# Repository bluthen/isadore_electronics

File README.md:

# isadore_electonics

Design files for the electronics of the Isadore Dryer Management System. Also included is what is called the MID software which queries the electronics and reports it back to the [isadore_server](https://github.com/bluthen/isadore_server/)

# Electronics Manufacture

Electronics manufactures usually want gerbers, centroid file, and a bill of materials. The latest pre-generated versions of these files can usually be found in the out directory (Example: `sensor_unitv3/out/`).

* The centroid and gerbers are in the zip file.
* The bill of materials is in the excel spreadsheet file (xlsx)
* An optional pins.png file may exist to show the manufacturer the location of pin1 for ICs.

Optionally you can generate the gerbers and centroid yourself depending by opening it up in [Eagle](https://www.autodesk.com/products/eagle/overview).

# Electronics Firmware

After you have a sensor unit or sensor hub, you need to program their firmware. To do this you need a AVR ISP programmer. Then there are script to help you program them. `sensor_unitv3/code/make.py`, `sensor_hubv3/code/Makefile`, and `fuse_crystal_clock.sh`.

*Note* you need a 5 pin ISP programmer. Most sold are 10 pin, so an adapter is needed.

To program the units or hubs you need some software installed:

* `avrdude`
* `gcc-avr`
* `avr-libc`

## Sensor Unit
A sensor unit can be programmed in many ways depending on what sensor modules you are going to plug into it.

Here is the help usage for `make.py`

```
Usage: make.py [OPTIONS] ADDRESS
  -h, --help                      Show this screen
  -d, --debug                     Debug build
  -p, --program                   Program unit
  -c, --clean                     Clean
  -f, --fuse                      Set fuse
  --prev303                       Build for prev3.03 unit
  --with-th                       Build with temperature humidty
  --with-pressurev1=m,b           Build in v1 pressure module
  --with-pressurev4a=cal_adjust   Build in v4a pressure module
  --with-pressurev4b=cal_adjust   Build in v4b pressure module
  --with-pressurev5=m,b           Build in v5 pressure module
  --with-anemometer               Build in Anemometer module
  --with-thermo                   Build in thermocouple module
  --with-multit                   Build in Multipoint-temp module
  --with-tach                     Build in tachometer module
```

So for example you might do with a unit, with the programmed placed and the unit powered.
```
python2 make.py -f -c -p --with-pressurev4b=0 102
```

If successful It is now programmed to use the pressurev4 module that gives you pressure/temperature/rh, and responses when address `102` is queried.

## Sensor Hub

To program the hub you would run with the programmer in place and powered:
```
cd sensor_hubv3/code
./fuse_crystal_clock.sh && make program
```

# MID (Master Interface Device)

This is basically the combination of a small computer (raspberry pi) and the hub electronics board. The hub and raspberry pi communicate serially. The hub has voltage regulators to power the raspberry pi.

## HUB<-> pi wiring

Notice for the power, Red is on TP1, and black is outside of usb connector.

Communication headers on pins 4 and 5 from outside corner.

## Install and configure raspbian

After installing raspian you'll want to set to enable access to the serail port with `raspi-config` and [disable the use of console by uart](https://www.raspberrypi.org/documentation/configuration/uart.md).

```
$ raspi-config
Interface Options->Serial->No->Yes
```

You'll also want to make sure the following are installed:

```
apt-get install python python-pip python-dev
pip install flask pytz requests restkit pyserial pymodbus numpy termcolor netifaces netaddr
```

## Troubleshooting
There is a script called `midsim.py` that can aid in troubleshooting. It allows you to query sensors from the command line. It is located at `sensor_hubv3/code/test/midsim.py` 

Below is the usage:

```
Usage: midsim.py [OPTION]...
  -h, --help            show this screen
  -v, --verbose         output verbose debug output
  -c, --continous=t,c   Keep pulling every t seconds, c many times c=0 for infinite
                        default is to pull once.
  -f, --format=format   The output format to use:
                        default:   The default style output
                        csv:       csv style output
  -t, --type=TYPE       TYPE=(temphum|anemometer|tachometer|thermocouple|pressure|pressurewide|
                              multipointreset|multipointc[1-4]|multipointaddrc[1-4]|ping|
                              unitversion|hubversion) *Required
  --get-cal             Get calibration value for type
  --set-cal=CAL_VALUE   Set calibration value for type
  -p, --port=PORT       PORT=#
  -a, --address=ADDRESS ADDRESS=#,#,#,...
  -u                    use udp instead of serial
  -d, --device=PATH     serial device to use for version 3, default /dev/ttyAMA0
  -o                    Use direct command code instead of general (aka version2)
  -j                    Just send commands then exit immediatly
  -s, --server=IP:PORT  Start midsim server listening on IP:PORT
  -r, --remote=IP:PORT  Query remote midsim server on IP:PORT

  address,port required except for --type=ping
  Max number of addresses is 32.
```

## Calibration
The main goal of the pressure modules was to report differencial pressure. The pressure module can be calibrated and there is a script to help with that process. It takes a large amounts of samples and sets an offset to match the reference. This script can be found at `sensor_hubv3/code/test/calibrator.py`

## Configure mid_software

Copy the mid_software to the raspberry pi. Copy `MID.cfg.example` to `MID.cfg` but one directory down from the location of mid_software. Modify MID.cfg for your needs. The most importanted are `baseurl` and `MIDpassword`Below is a reference for what each key means:

* `baseurl` The url to the base location of your running instance of [isadore_server](https://github.com/bluthen/isadore_server/).
* `MIDname` If you have multiple mids, this needs to be set so it knows which config to fetch. If it doesn't exist, all configs are fetched.
* `MIDpassword` The mid password that was set for your instance of isadore_server.
* `configpath` relative url where it should get the systems unit configuration. shouldn't need changing.
* `uploadpath` the relative url it should use to upload sensor data it gets. shouldn't need changing.
* `rcstatuspath` the relative url it uses for controls. shouldn't need changing.
* `hub_serial` the serial port to use to communicate with the hub electronics board. `/dev/ttyAMA0` on old raspberry pi's, `/dev/serial0` on new ones.
* `STORE_RAW_DATA_MODE` shouldn't need changing
* `RAW_DATA_LOC` shouldn't need changing
* `RS485_TIMEOUT` time out per unit. shouldn't need changing
* `RS485_BAUD` The serial baud rate to use. shouldn't need changing
* `enableRC_p` shouldn't need changing
* `mid_reading_interval_seconds` The minimal amount of time to pass before reading sensor data again.
* `log_level` The level to log at, can be `ERROR`, `WARNING`, or `DEBUG`
* `turn_off` If it should be not be activly getting readings and uploading them.

There are also some other configurations for specific temperature controls. For now for those parameters, please see the code to find them.

## Running mid_software

Put the following in the crontab of the user that is going to run mid_software on the MID. Replace the path to where you copied mid_software.

```
*/15 * * * * /home/pi/mid_software/processCheck.sh
*/10 * * * * /home/pi/mid_software/mid_log_check.sh
```

* `processCheck.sh` will start the process if it doesn't find it running.
* `mid_log_check.sh` tries to detect if the process locked up and will restart it, if it thinks it has.

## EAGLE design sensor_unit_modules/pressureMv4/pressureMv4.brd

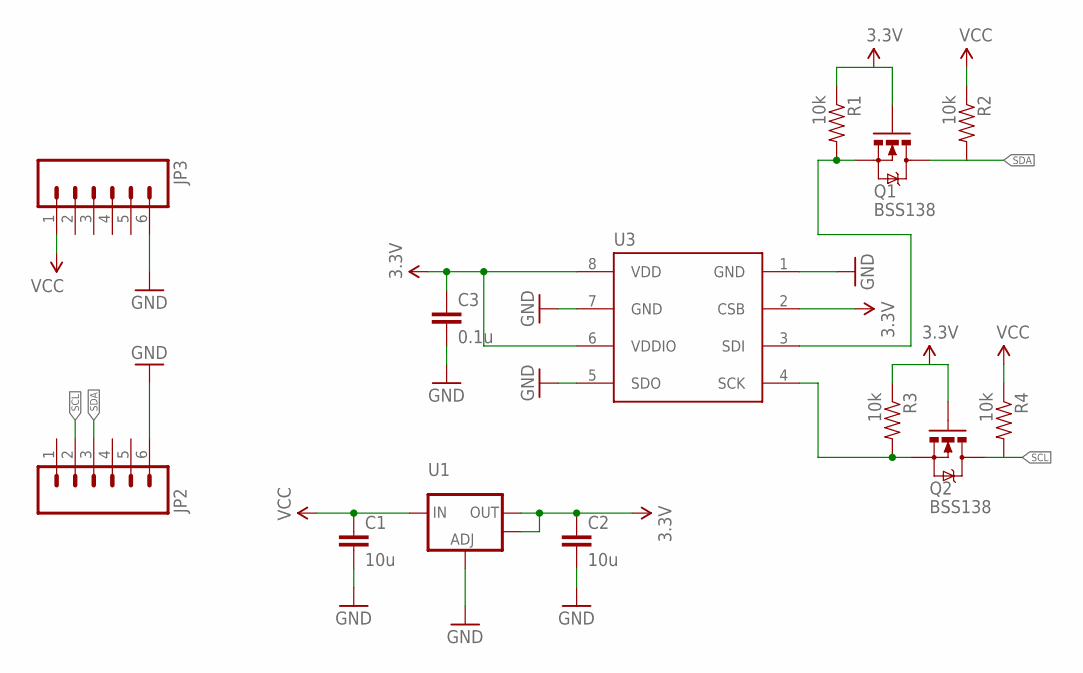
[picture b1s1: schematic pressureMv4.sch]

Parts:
C1, C2: 10u; 0805
C3: 0.1u; 0805
JP2, JP3: M06LOCK_LONGPADS; 1X06_LOCK_LONGPADS
Q1, Q2: BSS138; SOT323
R1, R2, R3, R4: 10k; 0805
U1: V_REG_LM1117SOT223; SOT223
U3: BME280SMD; BME280

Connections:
3.3V: C2.1, C3.1, Q1.1 (G), Q2.1 (G), R1.1, R3.1, U1.2 (OUT), U1.4 (OUT), U3.2 (CSB), U3.6 (VDDIO), U3.8 (VDD)
GND: C1.2, C2.2, C3.2, JP2.6, JP3.6, U1.1 (ADJ), U3.1 (GND), U3.5 (SDO), U3.7 (GND)
unnamed: Q1.2 (S), R1.2, U3.3 (SDI)
unnamed: Q2.2 (S), R3.2, U3.4 (SCK)
SCL: JP2.2, Q2.3 (D), R4.2
SDA: JP2.3, Q1.3 (D), R2.2
VCC: C1.1, JP3.1, R2.1, R4.1, U1.3 (IN)

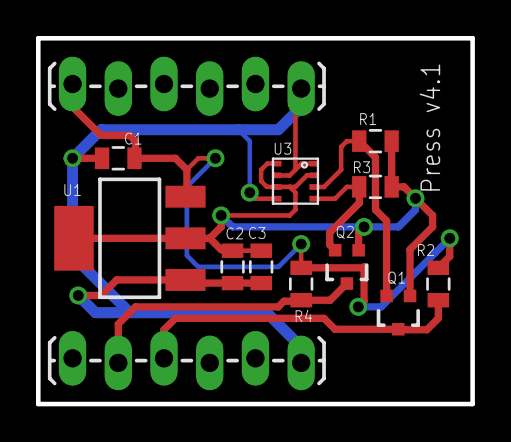
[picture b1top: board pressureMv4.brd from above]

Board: 2 copper layers, 24.1 x 20.3 mm, 13 parts (0 on the bottom side), 7 nets.

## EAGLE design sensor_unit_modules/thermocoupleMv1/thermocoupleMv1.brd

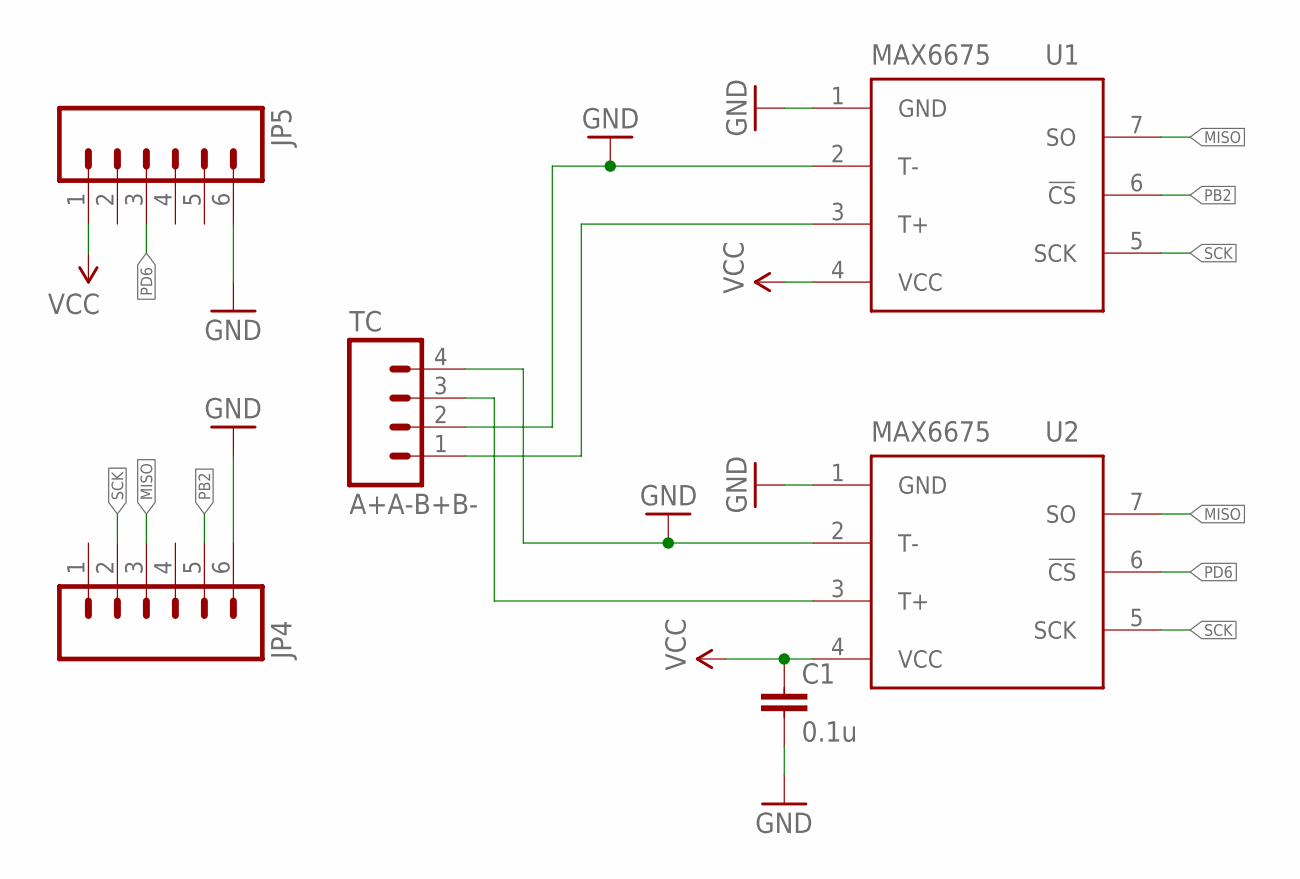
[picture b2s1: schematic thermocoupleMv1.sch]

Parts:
C1: 0.1u; 0805
JP4, JP5: M06LOCK_LONGPADS; 1X06_LOCK_LONGPADS
TC: A+A-B+B-; 1X04_LOCK_LONGPADS
U1, U2: MAX6675; SO08

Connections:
GND: C1.2, JP4.6, JP5.6, TC.2, TC.4, U1.1 (GND), U1.2 (T-), U2.1 (GND), U2.2 (T-)
MISO: JP4.3, U1.7 (SO), U2.7 (SO)
unnamed: TC.1, U1.3 (T+)
unnamed: TC.3, U2.3 (T+)
PB2: JP4.5, U1.6 (!CS)
PD6: JP5.3, U2.6 (!CS)
SCK: JP4.2, U1.5 (SCK), U2.5 (SCK)
VCC: C1.1, JP5.1, U1.4 (VCC), U2.4 (VCC)

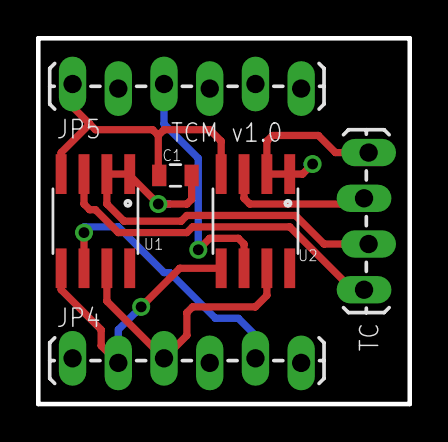
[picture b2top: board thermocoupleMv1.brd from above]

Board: 2 copper layers, 20.6 x 20.3 mm, 6 parts (0 on the bottom side), 8 nets.

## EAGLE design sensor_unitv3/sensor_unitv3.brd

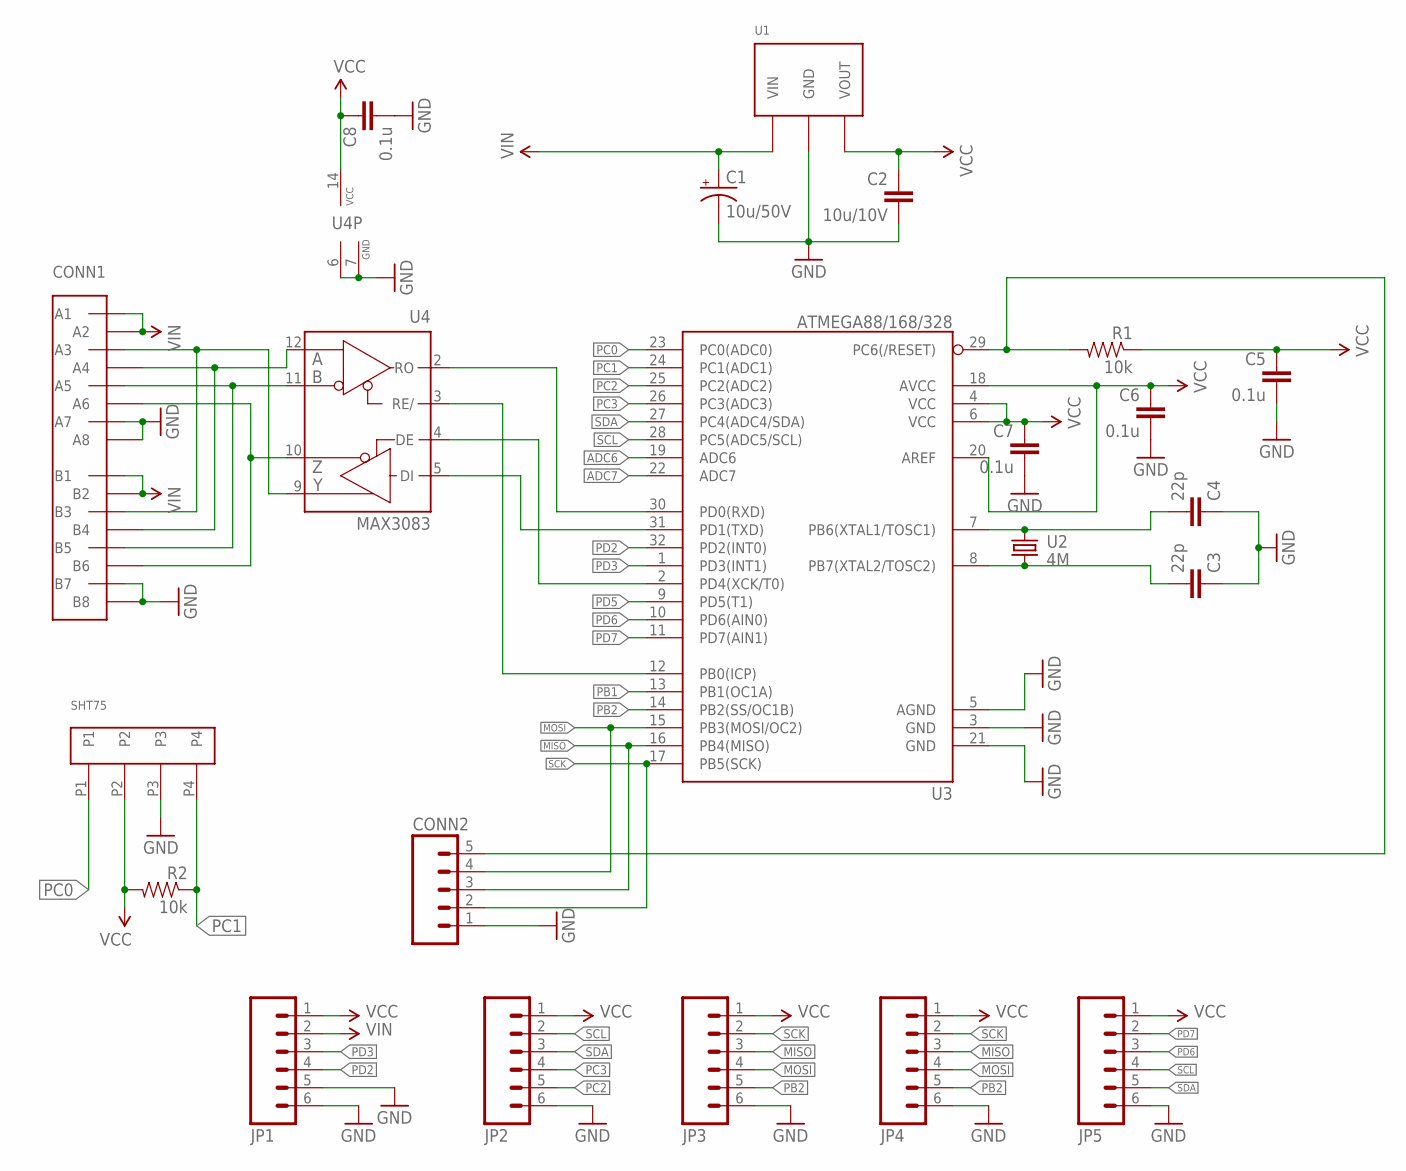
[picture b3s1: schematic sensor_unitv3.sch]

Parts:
C1: 10u/50V; PANASONIC_C
C2: 10u/10V; 0805
C3, C4: 22p; 0805
C5, C6, C7, C8: 0.1u; 0805
CONN1: 4UCON-04950
CONN2: M05LOCK; 1X05_LOCK
JP1, JP2, JP3, JP4, JP5: M06LOCK_LONGPADS; 1X06_LOCK_LONGPADS
R1, R2: 10k; 0805
SHT75: MM852-43-004-20; MM851-43-004-20
U1: OKI-78SR
U2: 4M; HC49UP
U3: ATMEGA88/168/328; TQFP32-08
U4: MAX3083; SO14

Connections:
ADC6: U3.19 (ADC6)
ADC7: U3.22 (ADC7)
C1U49: CONN1.A3, CONN1.B3, U4.9 (Y)
DE: U3.2 (PD4(XCK/T0)), U4.4 (DE)
DI: U3.31 (PD1(TXD)), U4.5 (DI)
GND: C1.-, C2.2, C3.1, C4.1, C5.2, C6.2, C7.2, C8.2, CONN1.A7, CONN1.A8, CONN1.B7, CONN1.B8, CONN2.1, JP1.5, JP1.6, JP2.6, JP3.6, JP4.6, JP5.6, SHT75.P3, U1.GND, U3.3 (GND), U3.5 (AGND), U3.21 (GND), U4.6 (GND), U4.7 (GND)
MISO: CONN2.3, JP3.3, JP4.3, U3.16 (PB4(MISO))
MOSI: CONN2.4, JP3.4, JP4.4, U3.15 (PB3(MOSI/OC2))
unnamed: C3.2, U2.1, U3.8 (PB7(XTAL2/TOSC2))
unnamed: C4.2, U2.2, U3.7 (PB6(XTAL1/TOSC1))
unnamed: CONN1.A5, CONN1.B5, U4.11 (B)
unnamed: CONN1.A4, CONN1.B4, U4.12 (A)
unnamed: CONN1.A6, CONN1.B6, U4.10 (Z)
PB1: U3.13 (PB1(OC1A))
PB2: JP3.5, JP4.5, U3.14 (PB2(SS/OC1B))
PC0: SHT75.P1, U3.23 (PC0(ADC0))
PC1: R2.1, SHT75.P4, U3.24 (PC1(ADC1))
PC2: JP2.5, U3.25 (PC2(ADC2))
PC3: JP2.4, U3.26 (PC3(ADC3))
PD2: JP1.4, U3.32 (PD2(INT0))
PD3: JP1.3, U3.1 (PD3(INT1))
PD5: U3.9 (PD5(T1))
PD6: JP5.3, U3.10 (PD6(AIN0))
PD7: JP5.2, U3.11 (PD7(AIN1))
RE: U3.12 (PB0(ICP)), U4.3 (RE/)
RESET: CONN2.5, R1.2, U3.29 (PC6(/RESET))
RO: U3.30 (PD0(RXD)), U4.2 (RO)
SCK: CONN2.2, JP3.2, JP4.2, U3.17 (PB5(SCK))
SCL: JP2.2, JP5.4, U3.28 (PC5(ADC5/SCL))
SDA: JP2.3, JP5.5, U3.27 (PC4(ADC4/SDA))
VCC: C2.1, C5.1, C6.1, C7.1, C8.1, JP1.1, JP2.1, JP3.1, JP4.1, JP5.1, R1.1, R2.2, SHT75.P2, U1.VOUT, U3.4 (VCC), U3.6 (VCC), U3.18 (AVCC), U3.20 (AREF), U4.14 (VCC)
VIN: C1.+, CONN1.A1, CONN1.A2, CONN1.B1, CONN1.B2, JP1.2, U1.VIN

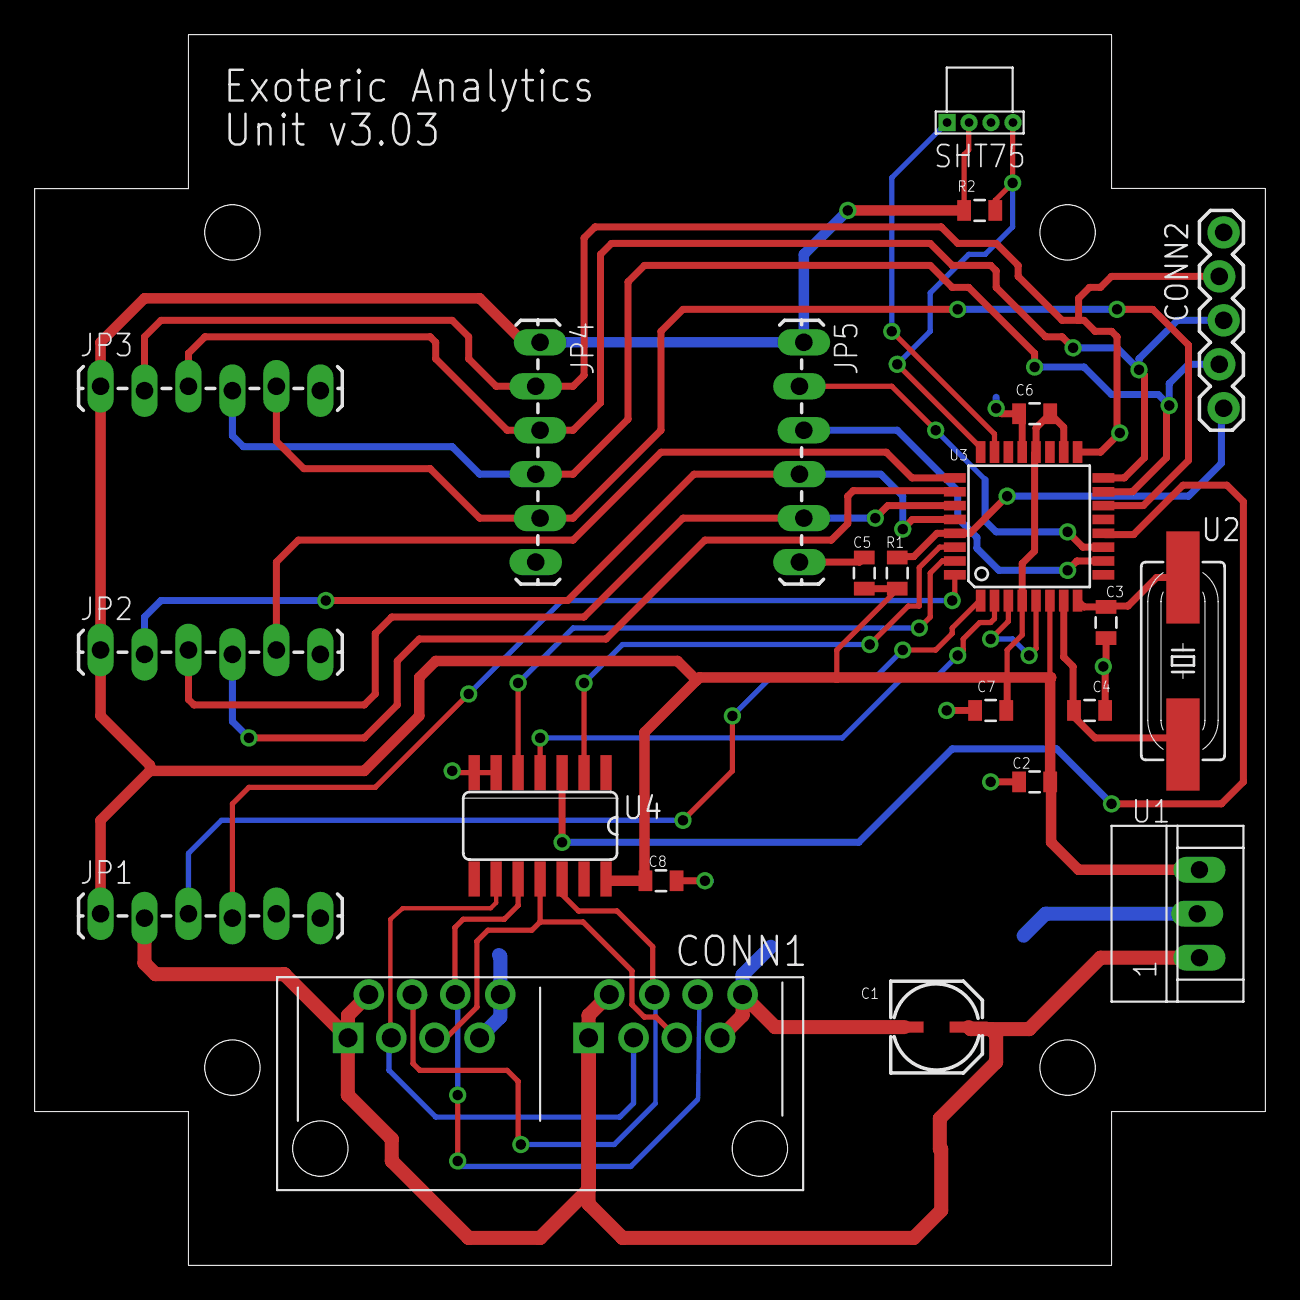
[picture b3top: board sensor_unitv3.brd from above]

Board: 2 copper layers, 71.1 x 71.1 mm, 22 parts (0 on the bottom side), 28 nets.

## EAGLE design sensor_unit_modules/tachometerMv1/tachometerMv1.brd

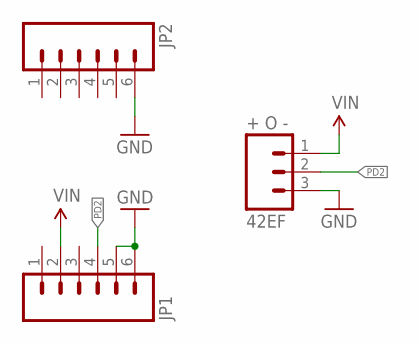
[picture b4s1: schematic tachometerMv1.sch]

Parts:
42EF: + O -; 1X03_LOCK_LONGPADS
JP1, JP2: M06LOCK_LONGPADS; 1X06_LOCK_LONGPADS

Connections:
GND: 42EF.3, JP1.5, JP1.6, JP2.6
PD2: 42EF.2, JP1.4
VIN: 42EF.1, JP1.2

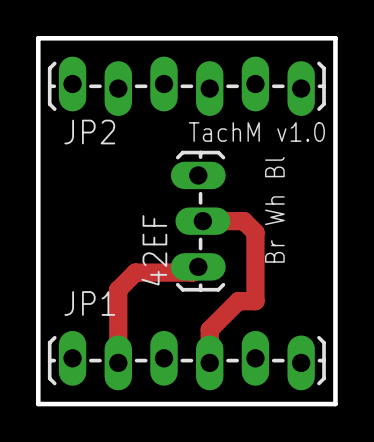
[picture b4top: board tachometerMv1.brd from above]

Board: 2 copper layers, 16.5 x 20.3 mm, 3 parts (0 on the bottom side), 3 nets.

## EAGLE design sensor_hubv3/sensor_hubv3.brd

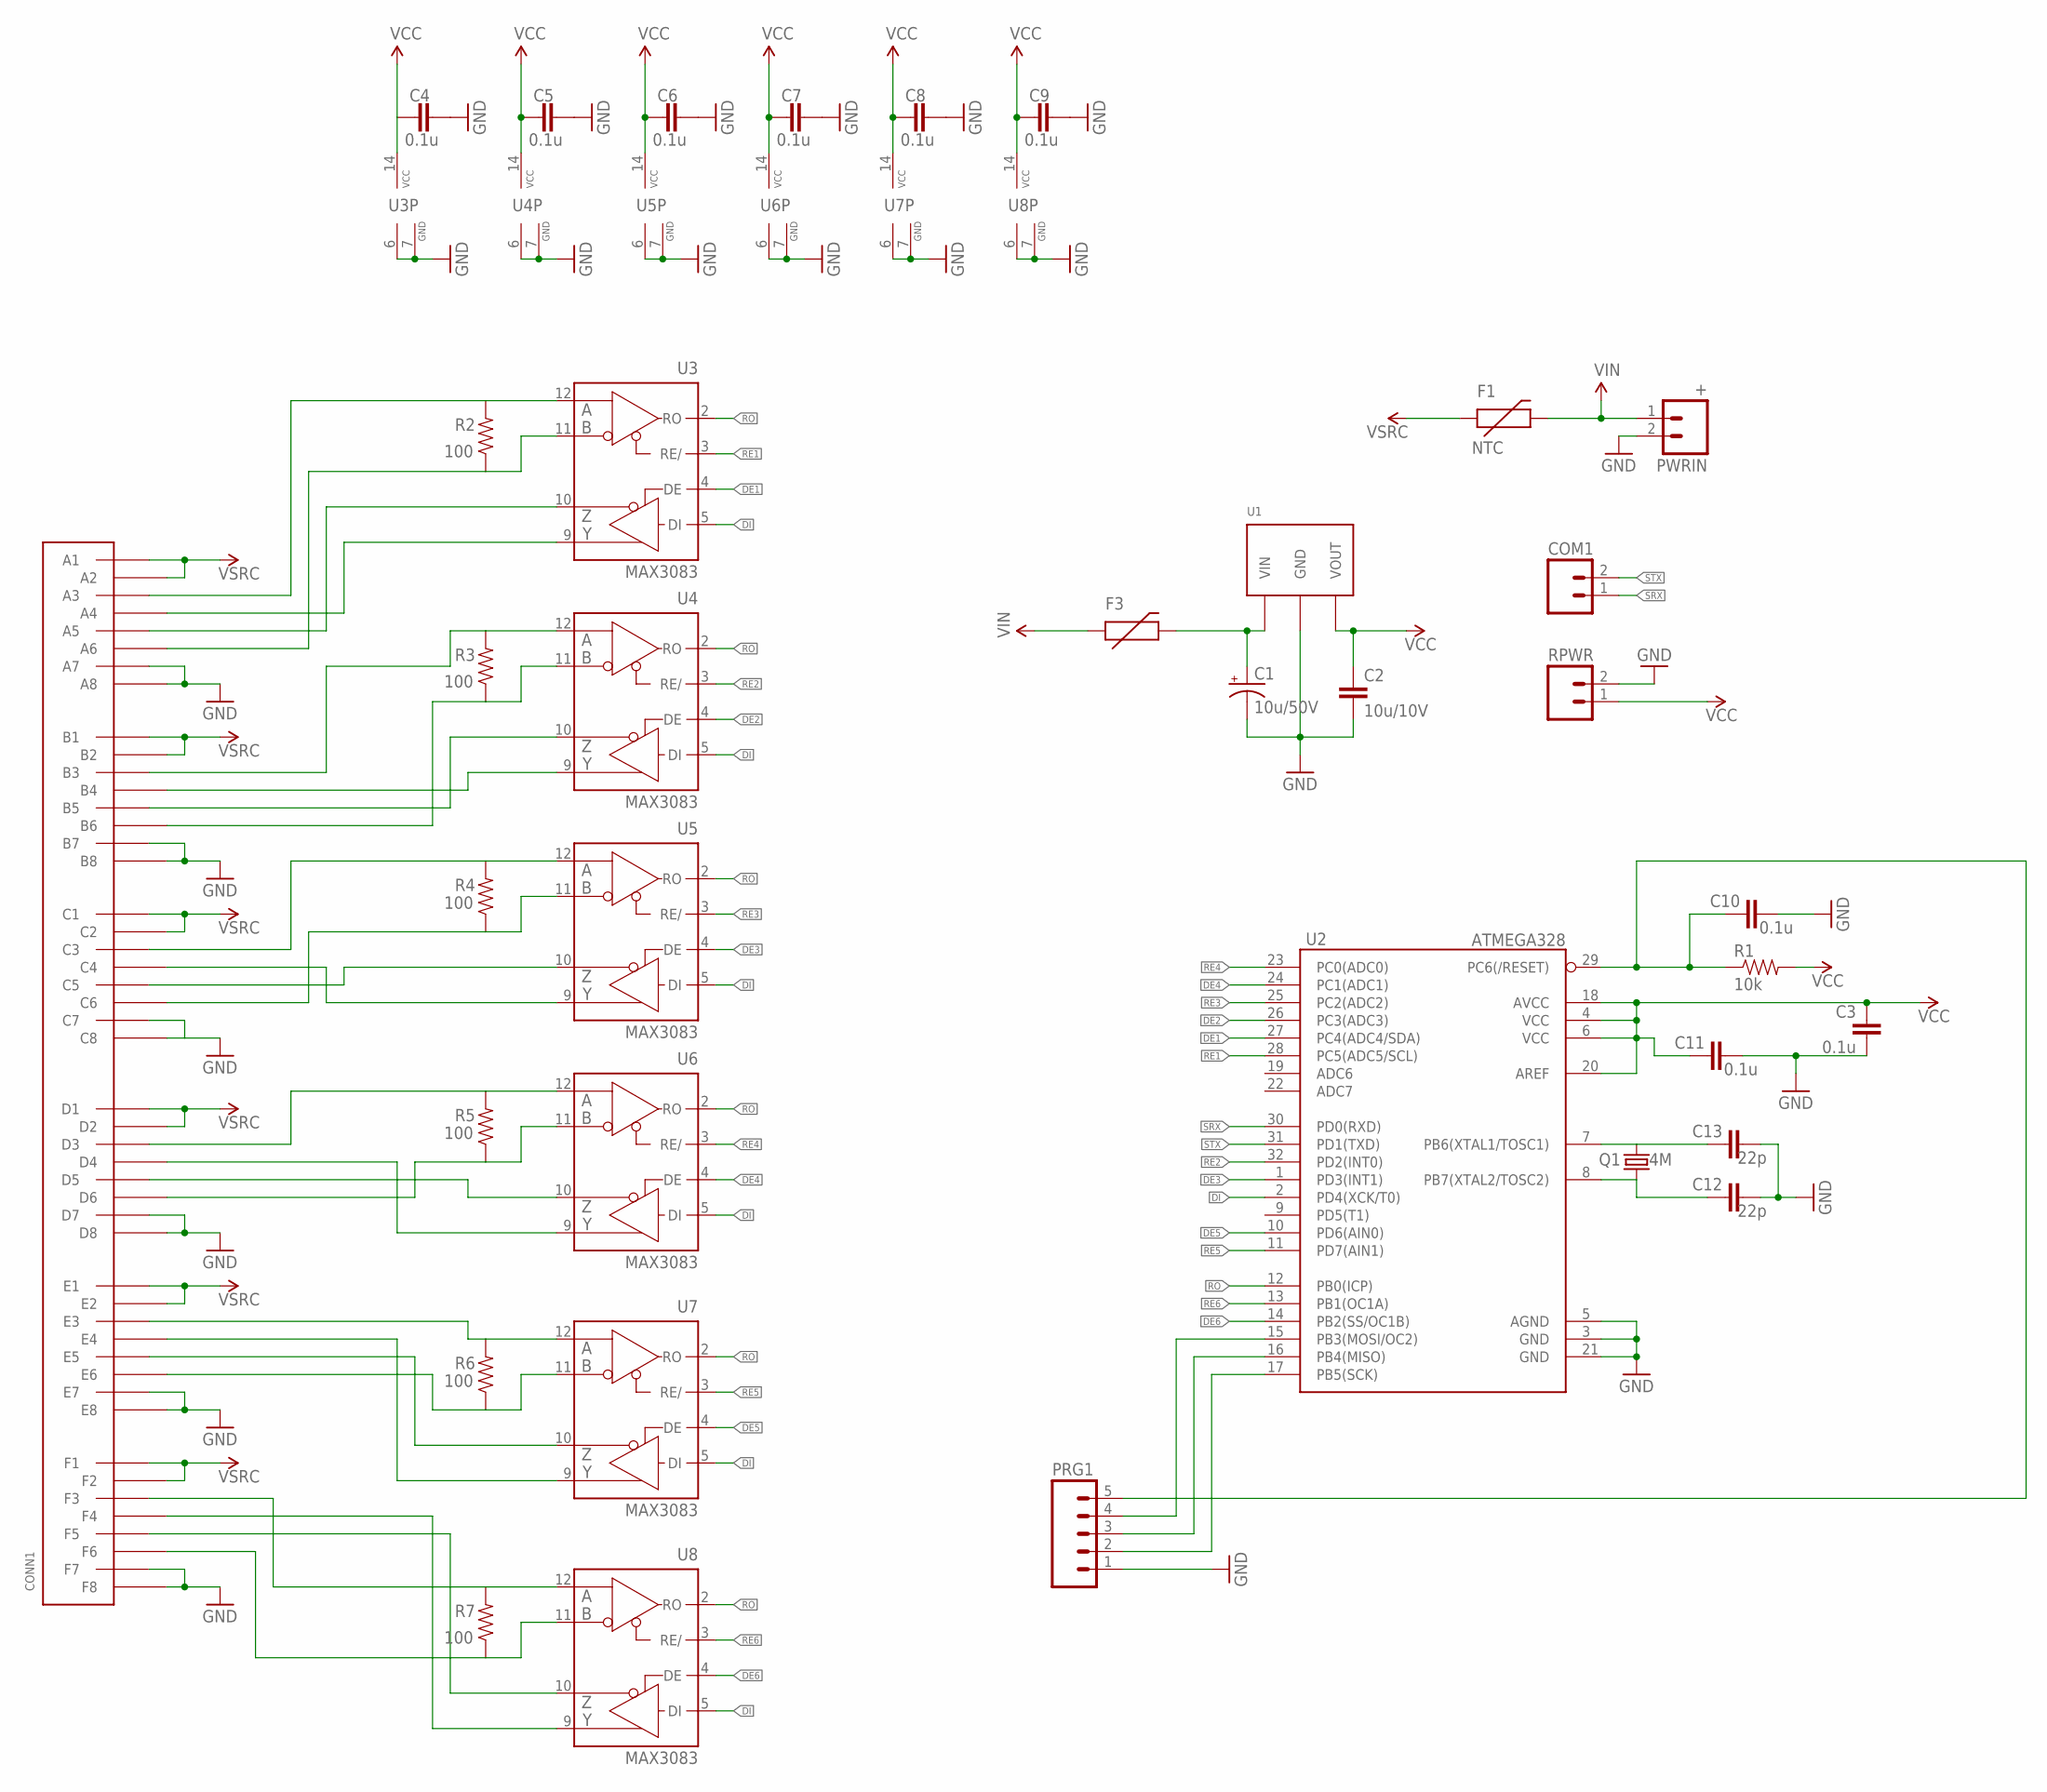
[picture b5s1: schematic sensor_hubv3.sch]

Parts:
C1: 10u/50V; PANASONIC_C
C2: 10u/10V; 0805
C3, C4, C5, C6, C7, C8, C9, C10, C11: 0.1u; 0805
C12, C13: 22p; 0805
COM1: M02LOCK_LONGPADS; 1X02_LOCK_LONGPADS
CONN1: 8P8C-6PORT; 4UCON-04953
F1: NTC; R-7,5
F3: PTC0603; 0603
PRG1: M05LOCK; 1X05_LOCK
PWRIN: +; SCREWTERMINAL-5MM-2
Q1: 4M; HC49UP
R1: 10k; 0805
R2, R3, R4, R5, R6, R7: 100; 0805
RPWR: M02LOCK_LONGPADS; 1X02_LOCK_LONGPADS
U1: OKI-78SR
U2: ATMEGA328; TQFP32-08
U3, U4, U5, U6, U7, U8: MAX3083; SO14

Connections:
DE1: U2.27 (PC4(ADC4/SDA)), U3.4 (DE)
DE2: U2.26 (PC3(ADC3)), U4.4 (DE)
DE3: U2.1 (PD3(INT1)), U5.4 (DE)
DE4: U2.24 (PC1(ADC1)), U6.4 (DE)
DE5: U2.10 (PD6(AIN0)), U7.4 (DE)
DE6: U2.14 (PB2(SS/OC1B)), U8.4 (DE)
DI: U2.2 (PD4(XCK/T0)), U3.5 (DI), U4.5 (DI), U5.5 (DI), U6.5 (DI), U7.5 (DI), U8.5 (DI)
GND: C1.-, C2.2, C3.1, C4.2, C5.2, C6.2, C7.2, C8.2, C9.2, C10.2, C11.2, C12.2, C13.2, CONN1.A7, CONN1.A8, CONN1.B7, CONN1.B8, CONN1.C7, CONN1.C8, CONN1.D7, CONN1.D8, CONN1.E7, CONN1.E8, CONN1.F7, CONN1.F8, PRG1.1, PWRIN.2, RPWR.2, U1.GND, U2.3 (GND), U2.5 (AGND), U2.21 (GND), U3.6 (GND), U3.7 (GND), U4.6 (GND), U4.7 (GND), U5.6 (GND), U5.7 (GND), U6.6 (GND), U6.7 (GND), U7.6 (GND), U7.7 (GND), U8.6 (GND), U8.7 (GND)
unnamed: CONN1.C4, U5.9 (Y)
unnamed: C13.1, Q1.2, U2.7 (PB6(XTAL1/TOSC1))
unnamed: C1.+, F3.2, U1.VIN
unnamed: C12.1, Q1.1, U2.8 (PB7(XTAL2/TOSC2))
unnamed: C10.1, PRG1.5, R1.1, U2.29 (PC6(/RESET))
unnamed: PRG1.4, U2.15 (PB3(MOSI/OC2))
unnamed: PRG1.3, U2.16 (PB4(MISO))
unnamed: PRG1.2, U2.17 (PB5(SCK))
unnamed: CONN1.A3, R2.2, U3.12 (A)
unnamed: CONN1.D6, R5.1, U6.11 (B)
unnamed: CONN1.C3, R4.2, U5.12 (A)
unnamed: CONN1.D3, R5.2, U6.12 (A)
unnamed: CONN1.E3, R6.2, U7.12 (A)
unnamed: CONN1.F3, R7.2, U8.12 (A)
unnamed: CONN1.A6, R2.1, U3.11 (B)
unnamed: CONN1.B6, R3.1, U4.11 (B)
unnamed: CONN1.C6, R4.1, U5.11 (B)
unnamed: CONN1.A5, U3.10 (Z)
unnamed: CONN1.E6, R6.1, U7.11 (B)
unnamed: CONN1.F6, R7.1, U8.11 (B)
unnamed: CONN1.B3, R3.2, U4.12 (A)
unnamed: CONN1.B5, U4.10 (Z)
unnamed: CONN1.C5, U5.10 (Z)
unnamed: CONN1.D5, U6.10 (Z)
unnamed: CONN1.E5, U7.10 (Z)
unnamed: CONN1.F5, U8.10 (Z)
unnamed: CONN1.A4, U3.9 (Y)
unnamed: CONN1.B4, U4.9 (Y)
unnamed: CONN1.D4, U6.9 (Y)
unnamed: CONN1.E4, U7.9 (Y)
unnamed: CONN1.F4, U8.9 (Y)
RE1: U2.28 (PC5(ADC5/SCL)), U3.3 (RE/)
RE2: U2.32 (PD2(INT0)), U4.3 (RE/)
RE3: U2.25 (PC2(ADC2)), U5.3 (RE/)
RE4: U2.23 (PC0(ADC0)), U6.3 (RE/)
RE5: U2.11 (PD7(AIN1)), U7.3 (RE/)
RE6: U2.13 (PB1(OC1A)), U8.3 (RE/)
RO: U2.12 (PB0(ICP)), U3.2 (RO), U4.2 (RO), U5.2 (RO), U6.2 (RO), U7.2 (RO), U8.2 (RO)
SRX: COM1.1, U2.30 (PD0(RXD))
STX: COM1.2, U2.31 (PD1(TXD))
VCC: C2.1, C3.2, C4.1, C5.1, C6.1, C7.1, C8.1, C9.1, C11.1, R1.2, RPWR.1, U1.VOUT, U2.4 (VCC), U2.6 (VCC), U2.18 (AVCC), U2.20 (AREF), U3.14 (VCC), U4.14 (VCC), U5.14 (VCC), U6.14 (VCC), U7.14 (VCC), U8.14 (VCC)
VIN: F1.P$2 (2), F3.1, PWRIN.1
VSRC: CONN1.A1, CONN1.A2, CONN1.B1, CONN1.B2, CONN1.C1, CONN1.C2, CONN1.D1, CONN1.D2, CONN1.E1, CONN1.E2, CONN1.F1, CONN1.F2, F1.P$1 (1)

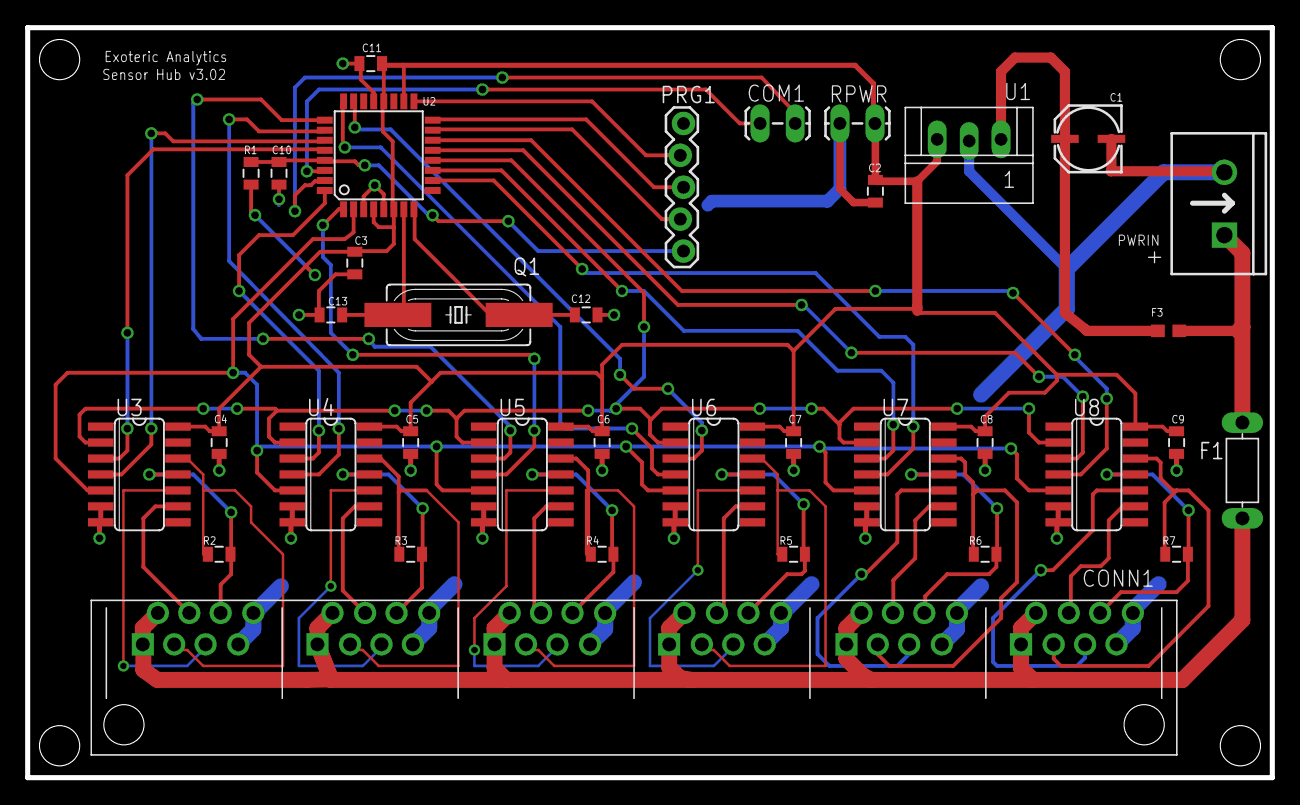
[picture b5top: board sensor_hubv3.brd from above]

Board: 2 copper layers, 99.1 x 59.7 mm, 36 parts (0 on the bottom side), 51 nets.

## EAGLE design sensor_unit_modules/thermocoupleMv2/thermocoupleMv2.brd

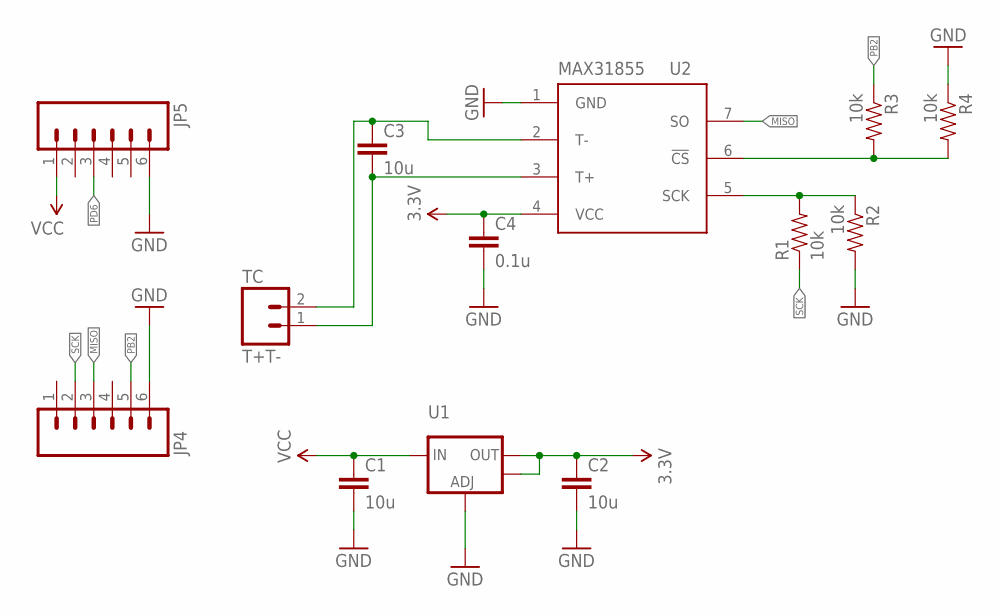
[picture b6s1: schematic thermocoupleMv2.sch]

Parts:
C1, C2, C3: 10u; 0805
C4: 0.1u; 0805
JP4, JP5: M06LOCK_LONGPADS; 1X06_LOCK_LONGPADS
R1, R2, R3, R4: 10k; 0805
TC: T+T-; 1X02_LOCK_LONGPADS
U1: V_REG_LM1117SOT223; SOT223
U2: MAX31855; SO08

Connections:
3.3V: C2.1, C4.1, U1.2 (OUT), U1.4 (OUT), U2.4 (VCC)
GND: C1.2, C2.2, C4.2, JP4.6, JP5.6, R2.2, R4.1, U1.1 (ADJ), U2.1 (GND)
MISO: JP4.3, U2.7 (SO)
unnamed: C3.2, TC.1, U2.3 (T+)
unnamed: R1.2, R2.1, U2.5 (SCK)
unnamed: C3.1, TC.2, U2.2 (T-)
unnamed: R3.2, R4.2, U2.6 (!CS)
PB2: JP4.5, R3.1
PD6: JP5.3
SCK: JP4.2, R1.1
VCC: C1.1, JP5.1, U1.3 (IN)

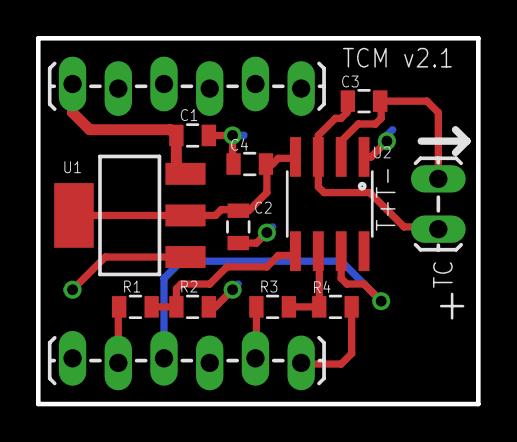
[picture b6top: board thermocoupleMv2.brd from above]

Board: 2 copper layers, 24.4 x 20.3 mm, 13 parts (0 on the bottom side), 10 nets.

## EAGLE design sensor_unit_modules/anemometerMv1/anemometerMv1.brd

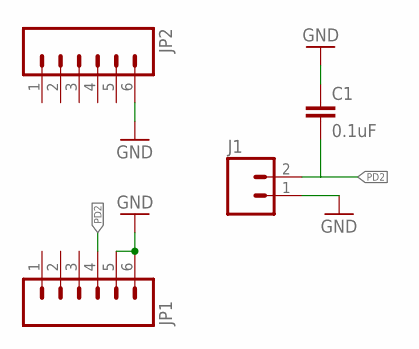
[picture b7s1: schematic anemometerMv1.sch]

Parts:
C1: 0.1uF; 0805-CAP
J1: M02LOCK_LONGPADS; 1X02_LOCK_LONGPADS
JP1, JP2: M06LOCK_LONGPADS; 1X06_LOCK_LONGPADS

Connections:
GND: C1.1, J1.1, JP1.5, JP1.6, JP2.6
PD2: C1.2, J1.2, JP1.4

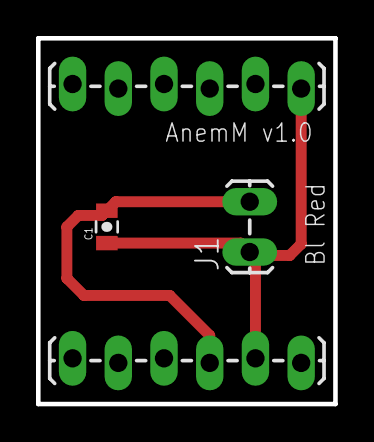
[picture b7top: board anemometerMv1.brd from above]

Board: 2 copper layers, 16.5 x 20.3 mm, 4 parts (0 on the bottom side), 2 nets.

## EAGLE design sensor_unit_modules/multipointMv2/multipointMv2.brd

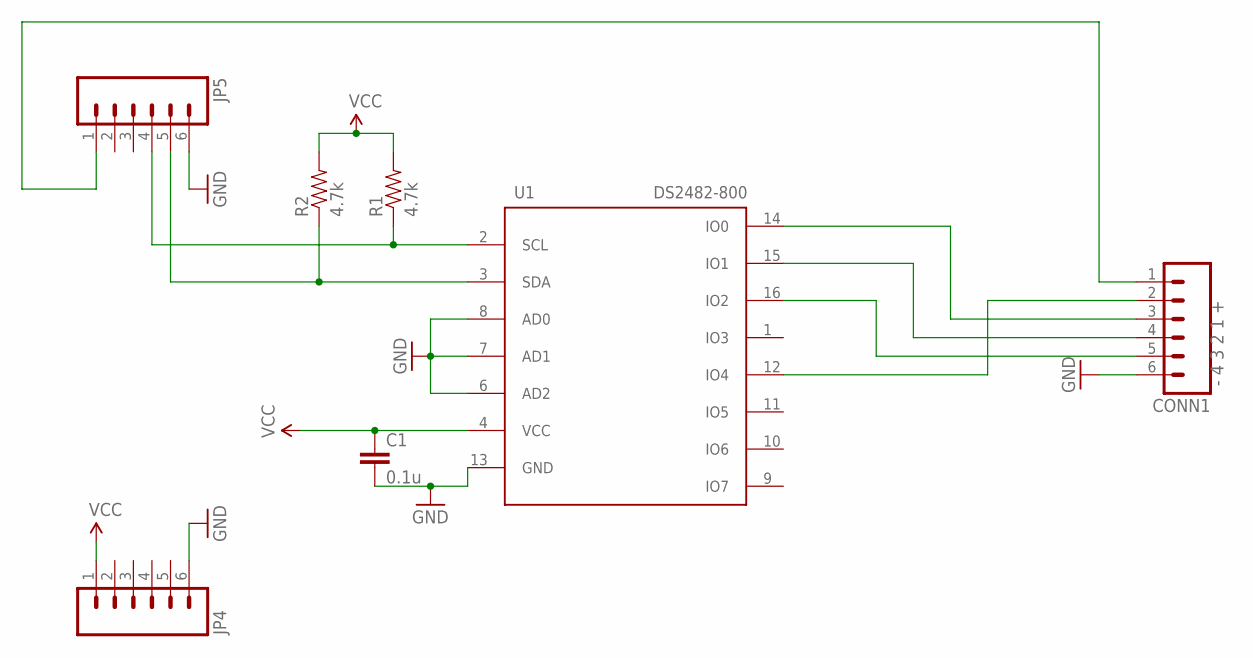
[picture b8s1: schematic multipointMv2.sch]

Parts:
C1: 0.1u; 0805
CONN1: - 4 3 2 1 +; 1X06_LOCK_LONGPADS
JP4, JP5: M06LOCK_LONGPADS; 1X06_LOCK_LONGPADS
R1, R2: 4.7k; 0805
U1: DS2482-800; SO16

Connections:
GND: C1.2, CONN1.6, JP4.6, JP5.6, U1.6 (AD2), U1.7 (AD1), U1.8 (AD0), U1.13 (GND)
unnamed: CONN1.5, U1.16 (IO2)
unnamed: CONN1.4, U1.15 (IO1)
unnamed: CONN1.3, U1.14 (IO0)
unnamed: CONN1.2, U1.12 (IO4)
unnamed: CONN1.1, JP5.1
SCL: JP5.4, R1.1, U1.2 (SCL)
SDA: JP5.5, R2.1, U1.3 (SDA)
VCC: C1.1, JP4.1, R1.2, R2.2, U1.4 (VCC)

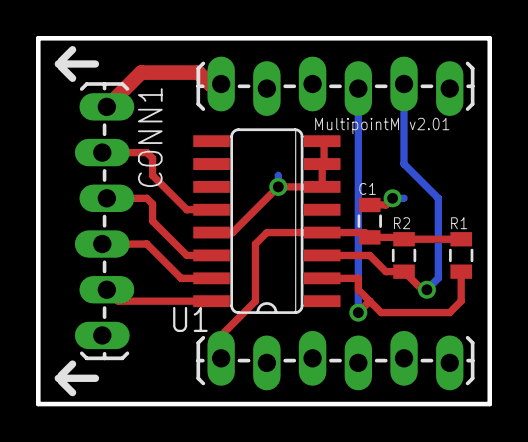
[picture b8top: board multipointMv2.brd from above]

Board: 2 copper layers, 25.1 x 20.3 mm, 7 parts (0 on the bottom side), 9 nets.

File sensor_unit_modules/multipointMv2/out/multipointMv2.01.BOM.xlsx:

Labels | Part | Primary Source | Secondary Source | Notes
U1 | SO16 DS2482S-800 1-wire bridge | Digikey: DS2482S-800+-ND | Mouser: 700-DS2482S-800
R1, R2 | 0805 4.7k Ohm resistor | Digikey: 311-4.7KARCT-ND
C1 | 0805 0.1uF capacitor 10V | Digikey: 478-3755-1-ND
JP4, JP5 | 0.1" male headers 6conn | Digikey: A26514-40-ND |  | Mounted on the back
CONN1 | 0.1" 6 pos screw terminal block | Digikey: A98337-ND

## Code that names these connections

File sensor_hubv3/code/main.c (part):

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
//RS485 enable pins
//Port 1
#define RSP1RE PC5
#define RSP1REPORT PORTC
#define RSP1REDDR DDRC
#define RSP1DE PC4
#define RSP1DEPORT PORTC
#define RSP1DEDDR DDRC

//Port 2
#define RSP2RE PD2
#define RSP2REPORT PORTD
#define RSP2REDDR DDRD
#define RSP2DE PC3
#define RSP2DEDDR DDRC
#define RSP2DEPORT PORTC

//Port 3
#define RSP3RE PC2
#define RSP3REPORT PORTC
#define RSP3REDDR DDRC
#define RSP3DE PD3
#define RSP3DEPORT PORTD
#define RSP3DEDDR DDRD

//Port 4
#define RSP4RE PC0
#define RSP4REPORT PORTC
#define RSP4REDDR DDRC
#define RSP4DE PC1
#define RSP4DEPORT PORTC
#define RSP4DEDDR DDRC

//Port 5
#define RSP5RE PD7
#define RSP5REPORT PORTD
#define RSP5REDDR DDRD
#define RSP5DE PD6
#define RSP5DEPORT PORTD
#define RSP5DEDDR DDRD

//Port 6
#define RSP6RE PB1
#define RSP6REPORT PORTB
#define RSP6REDDR DDRB
#define RSP6DE PB2
#define RSP6DEPORT PORTB
#define RSP6DEDDR DDRB

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	//Turn on watch dog
	wdt_enable(WDTO_8S);
	sei(); //Enable interrupts
	DDRD &=~_BV(PD0); //Read on hw rx usart 
	DDRD |= _BV(PD1);

	//Hardware USART
	UBRR0H = UBRRH_VALUE;
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
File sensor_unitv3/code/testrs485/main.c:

#define BAUD 9600

#include <stdio.h>
#include <avr/io.h>
#include <avr/interrupt.h>
#include <util/delay.h>
#include <util/setbaud.h>
#include <util/crc16.h>

#include "softuart.h"

#define RS485RE PB0
#define RS485REPORT PORTB
#define RS485REDDR DDRB
#define RS485DE PD4
#define RS485DEPORT PORTD
#define RS485DEDDR DDRD

static void ioinit(void);
static int uart_putchar(char c, FILE *stream);
static uint8_t uart_getchar(void);
static int swuart_putchar( char c, FILE *stream );
static FILE mystdout = FDEV_SETUP_STREAM(uart_putchar, NULL, _FDEV_SETUP_WRITE);
static FILE suart_stream = FDEV_SETUP_STREAM(swuart_putchar, NULL, _FDEV_SETUP_WRITE );

int main(void)
{
	uint16_t time = 0;
	uint16_t count = 0;
	unsigned char c = 0;
	ioinit();
	fprintf(stderr, "Unit rs485 test listening on rs485...\r\n");
	//DEBUG
	//turn on to rs485
	RS485DEPORT |=_BV(RS485DE); //DE is enabled when high
	fprintf(stderr, "DE on\r\n");
	while(1)
	{

		while (UCSR0A & (1<< RXC0))
		{
			c=UDR0;
			fprintf(stderr, "R: %c\r\n", c);
		}
		if(time >= 50000)
		{
			fprintf(stderr, "UC: %d\r\n", count);
			fprintf(stdout, "UC: %d\r\n", count);
			time=0;
			count++;
		}
		_delay_us(100);
		time++;
	}
}

void ioinit(void)
{
	softuart_init();
	sei(); //enable interupts
	DDRD &=~_BV(PD0); // read on usart RX pin
	DDRD |=_BV(PD1); // output on usart TX pin
	UBRR0H = UBRRH_VALUE;
	UBRR0L = UBRRL_VALUE;
	//UCSR0B = (1 << RXEN0)|(1<<TXEN0)|(1<<RXCIE0);
	UCSR0B = (1 << RXEN0)|(1<<TXEN0);
	stdout = &mystdout;
	stderr = &suart_stream;
	//Set RE and DE to outputs
	RS485REDDR |= _BV(RS485RE);
	RS485DEDDR |= _BV(RS485DE);
	//Enable RE, disable DE
	RS485REPORT &=~_BV(RS485RE); //RE is enabled when low
	RS485DEPORT &=~_BV(RS485DE); //DE is disabled when low
}


/*
 * Get character from serial
 */
uint8_t uart_getchar(void)
{
	while( !(UCSR0A & (1<<RXC0)) );
	return(UDR0);
}


/*
 * Send character to serial
 */
static int uart_putchar(char c, FILE *stream)
{
	//if (c == '\n') uart_putchar('\r', stream);

	loop_until_bit_is_set(UCSR0A, UDRE0);
	UDR0 = c;

	return 0;
}



// interface between avr-libc stdio and the modified Fleury uart-lib:
static int swuart_putchar( char c, FILE *stream )
{
	if ( c == '\n' ) {
		softuart_putchar( '\r' );
	}
	softuart_putchar( c );

	return 0;
}

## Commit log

2019-08-26 Added more instructions to the README.md
2019-08-26 more README.md instructions
2019-08-26 Added some mid_software documentation.
2020-08-10 Sensor unit bme 5.10. A cheaper T/RH/P sensor unit backward compatible
2020-08-11 Updated assembly bom, and pictures.
2021-06-27 Supports using PB5(SCK) as anemometer pin with software debounce as alternative to module.
2023-07-21 Added raw data protocol pdf
2023-07-21 MID(HUB) <-> Unit Pinout diagram

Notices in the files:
sensor_hubv3/code/main.c:
Copyright 2010-2019 Dan Elliott, Russell Valentine
Licensed under the Apache License, Version 2.0 (the "License");
parts and their libraries:
SparkFun-DigitalIC: Licensing: CC v3.0 Share-Alike You are welcome to use this library for commercial purposes.
SparkFun-Connectors: Licensing: Creative Commons ShareAlike 4.0 International - https://creativecommons.org/licenses/by-sa/4.0
